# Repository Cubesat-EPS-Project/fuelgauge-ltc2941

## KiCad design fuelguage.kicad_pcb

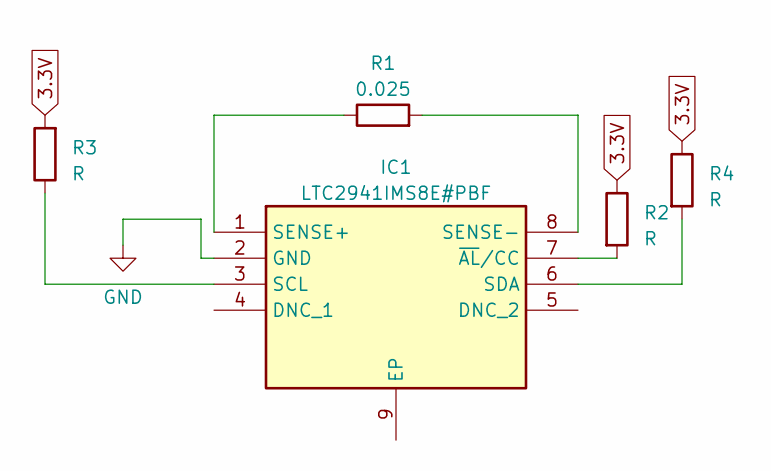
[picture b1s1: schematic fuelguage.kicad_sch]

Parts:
IC1: LTC2941IMS8E#PBF; SOP65P490X110-9N; Mouser Part Number 584-LTC2941IMS8E#PBF
R1: 0.025; CRA2512-FZ-R025ELF
R2, R3, R4: R; RESC2012X65N

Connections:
3.3V: R2.1, R3.2, R4.1
GND: IC1.2 (GND)
unnamed: IC1.3 (SCL), R3.1
unnamed: IC1.6 (SDA), R4.2
unnamed: IC1.1 (SENSE+), R1.1
unnamed: IC1.8 (SENSE-), R1.2
unnamed: IC1.7 (~AL/CC), R2.2

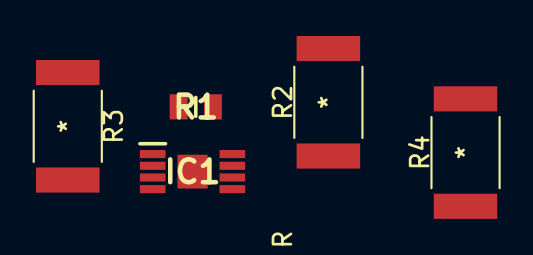
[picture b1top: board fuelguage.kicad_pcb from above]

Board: 2 copper layers, 5 parts (0 on the bottom side), 6 nets.

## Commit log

2023-03-20 INIT
2023-06-02 prep for final

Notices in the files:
parts and their libraries:
Copyright 2021 Accelerated Designs. All rights reserved.
